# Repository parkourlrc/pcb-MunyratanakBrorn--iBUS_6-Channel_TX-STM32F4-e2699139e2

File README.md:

# iBUS_6-Channel_TX-STM32F4
iBUS Remote Controller using nRF24l01+

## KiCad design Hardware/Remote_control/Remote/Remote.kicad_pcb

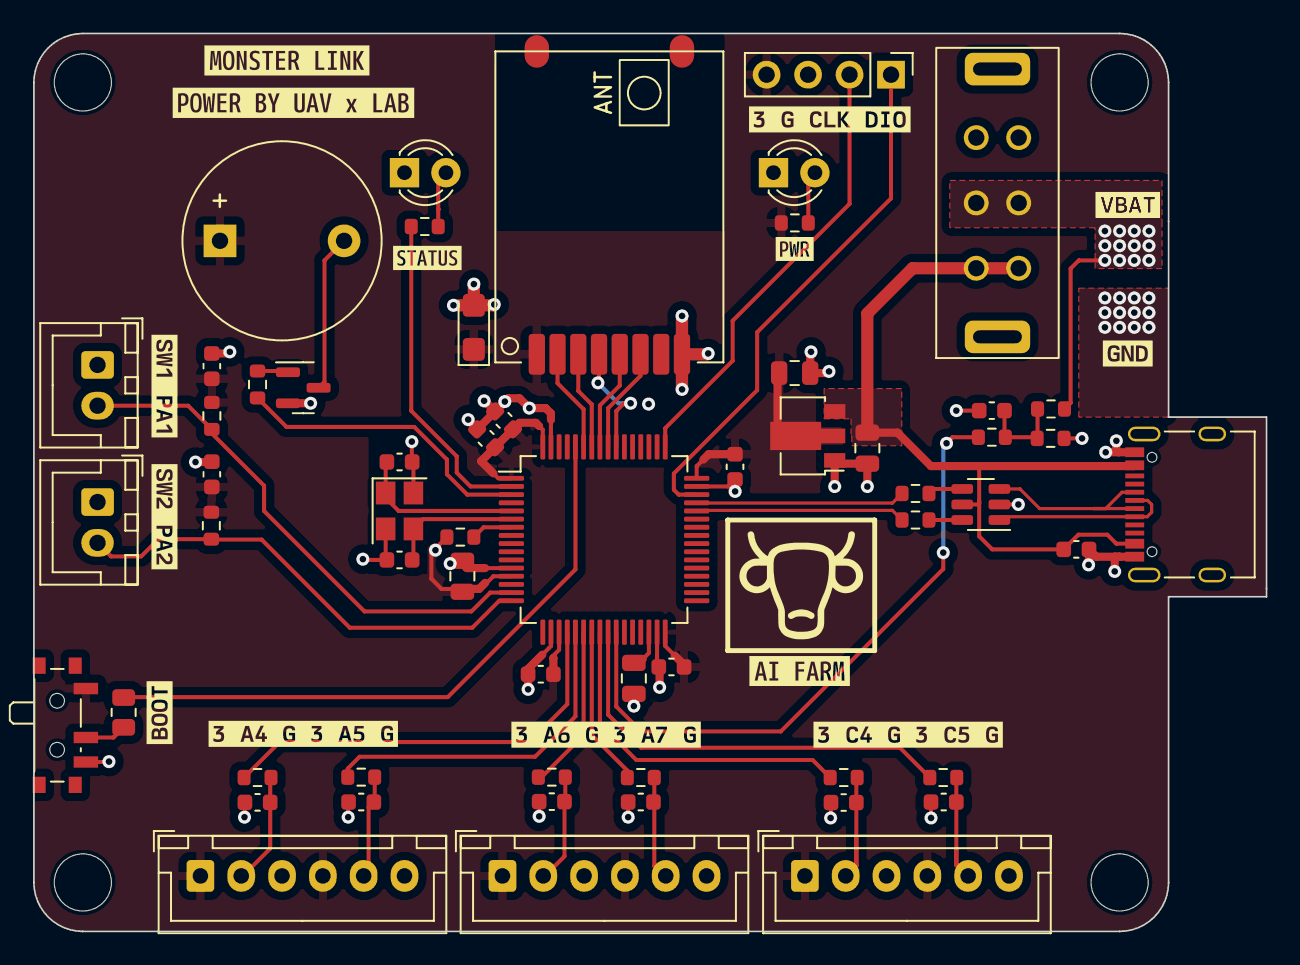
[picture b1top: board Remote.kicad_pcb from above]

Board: 2 copper layers, 75.5 x 55.0 mm, 77 parts (0 on the bottom side), 45 nets.

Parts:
BZ1: Buzzer; Buzzer_12x9.5RM7.6
C1, C6, C7, C8, C9, C10, C16, C17, C18, C19, C20, C21, C22, C24, C25: 100nf; C_0603_1608Metric
C3, C11: 4.7uF; C_0805_2012Metric
C5: 100nf; C_0805_2012Metric
C12: 2.2uF; C_0805_2012Metric
C13, C14: 22PF; C_0603_1608Metric
C15: 4.7UF; CP_EIA-3216-12_Kemet-S
D2, D3: LED; LED_D3.0mm
H1, H2, H3, H4: MountingHole; MountingHole_3.5mm
J1: USB_C_Receptacle_USB2.0; USB_C_Receptacle_Palconn_UTC16-G
J2: SL_LINK; PinHeader_1x04_P2.54mm_Vertical
J3, J5, J6: ADC; JST_XH_B6B-XH-A_1x06_P2.50mm_Vertical
J4, J8: SW; JST_XH_B2B-XH-A_1x02_P2.50mm_Vertical
Q1: 1P; SOT-23
R1, R4: 22; R_0603_1608Metric
R2, R5, R11, R12, R13, R14, R15, R16, R17: 1K; R_0603_1608Metric
R3: 4.7K; R_0603_1608Metric
R6, R9: 1k; R_0603_1608Metric
R7: 10k; R_0805_2012Metric
R8: 10k; R_0603_1608Metric
R10: 470R; R_0603_1608Metric
R18: 3K; R_0603_1608Metric
SW1: SW_SPDT; SW_SPDT_PCM12
U2: STM32F401RCTx; LQFP-64_10x10mm_P0.5mm
U3: AMS1117-3.3; SOT-89-3
U4: AS01-SPI
U5: USBLC6-2SC6; SOT-23-6
U6: Slide-Switch
Y1: 8Mhz; Crystal_SMD_3225-4Pin_3.2x2.5mm
kibuzzard-64B61BBF, kibuzzard-64B61BBF#2: G***; kibuzzard-64B61BBF
kibuzzard-64B61BC8: G***; kibuzzard-64B61BC8
kibuzzard-64B63D2D: G***; kibuzzard-64B63D2D
kibuzzard-64B63D22: G***; kibuzzard-64B63D22
kibuzzard-64B63D40: G***; kibuzzard-64B63D40
kibuzzard-64B634B2: G***; kibuzzard-64B634B2
kibuzzard-64B63325: G***; kibuzzard-64B63325
kibuzzard-64B63473: G***; kibuzzard-64B63473
kibuzzard-64B63542: G***; kibuzzard-64B63542
kibuzzard-64C36C76: G***; kibuzzard-64C36C76
kibuzzard-64C36CB1: G***; kibuzzard-64C36CB1
kibuzzard-64C36CD5: G***; kibuzzard-64C36CD5
kibuzzard-64C36D1E: G***; kibuzzard-64C36D1E
kibuzzard-64C36D15: G***; kibuzzard-64C36D15

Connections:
+3.3V: BZ1.1 (-), C5.2, C6.2, C7.2, C8.2, C9.2, C10.2, C11.1, C15.1, C24.1, C25.1, J2.4, J3.1, J3.4, J5.1, J5.4, J6.1, J6.4, R6.1, R8.1, R11.2, R12.2, SW1.1 (A), U2.1 (VBAT), U2.13 (VREF+), U2.19 (VDD), U2.32 (VDD), U2.48 (VDD), U2.64 (VDD), U3.2 (VO), U4.1 (VCC)
+5V: C3.1, C16.2, J1.A4 (VBUS), J1.A9 (VBUS), J1.B4 (VBUS), J1.B9 (VBUS), U3.3 (VI), U5.5 (VBUS), U6.1, U6.4
/ADC1: C17.2, J3.5, R5.2
/ADC2: C18.2, J3.2, R13.2
/ADC3: C19.2, J5.2, R14.2
/ADC4: C20.2, J5.5, R15.2
/ADC5: C21.2, J6.2, R16.2
/ADC6: C22.2, J6.5, R17.2
/ADC_PA4: R13.1, U2.20 (PA4)
/ADC_PA5: R5.1, U2.21 (PA5)
/ADC_PA6: R14.1, U2.22 (PA6)
/ADC_PA7: R15.1, U2.23 (PA7)
/ADC_PB0: R2.1, U2.26 (PB0)
/ADC_PC4: R16.1, U2.24 (PC4)
/ADC_PC5: R17.1, U2.25 (PC5)
/BOOT0: R7.1, U2.60 (BOOT0)
/CE_PB7: U2.59 (PB7), U4.2 (CE)
/CLK: J2.2, U2.49 (PA14)
/CSN_PB6: U2.58 (PB6), U4.3 (CSN)
/DIO: J2.1, U2.46 (PA13)
/LED: R9.1, U2.2 (PC13)
/MISO_PB4: U2.56 (PB4), U4.6 (MISO)
/MOSI_PB5: U2.57 (PB5), U4.5 (MOSI)
/NRST: R8.2, U2.7 (NRST)
/OSC_IN: C13.1, U2.5 (PH0), Y1.1
/OSC_OUT: C14.1, U2.6 (PH1), Y1.3
/PA1_SW1: J8.2, R12.1, U2.15 (PA1)
/PA2_SW2: J4.2, R11.1, U2.16 (PA2)
/PC14_BUZZER: R10.1, U2.3 (PC14)
/SCK_PB3: U2.55 (PB3), U4.4 (CLK)
/USB_IN+: J1.A6 (D+), J1.B6 (D+), U5.3 (I/O2)
/USB_IN-: J1.A7 (D-), J1.B7 (D-), U5.1 (I/O1)
/USB_OUT+: R1.2, U2.45 (PA12)
/USB_OUT-: R4.1, U2.44 (PA11)
/VBAT: R3.2, U6.2, U6.5
/VBAT_MEASURE: C1.2, R2.2, R3.1, R18.2
GND: C1.1, C3.2, C5.1, C6.1, C7.1, C8.1, C9.1, C10.1, C11.2, C12.2, C13.2, C14.2, C15.2, C16.1, C17.1, C18.1, C19.1, C20.1, C21.1, C22.1, C24.2, C25.2, D2.1 (K), D3.1 (K), J1.A1 (GND), J1.A12 (GND), J1.B1 (GND), J1.B12 (GND), J1.S1 (SHIELD), J2.3, J3.3, J3.6, J4.1, J5.3, J5.6, J6.3, J6.6, J8.1, Q1.2 (E), R18.1, SW1.3 (C), U2.12 (VSSA), U2.18 (VSS), U2.31 (VSS), U2.47 (VSS), U2.63 (VSS), U3.1 (GND), U4.8 (GND), U5.2 (GND), Y1.2, Y1.4
unnamed: BZ1.2 (+), Q1.3 (C)
unnamed: D2.2 (A), R6.2
unnamed: D3.2 (A), R9.2
unnamed: Q1.1 (B), R10.2
unnamed: R1.1, U5.4 (I/O2)
unnamed: R4.2, U5.6 (I/O1)
unnamed: R7.2, SW1.2 (B)
unnamed: C12.1, U2.30 (VCAP1)

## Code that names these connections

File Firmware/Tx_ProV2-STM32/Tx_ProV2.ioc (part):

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Mcu.Name=STM32F401R(B-C)Tx
Mcu.Package=LQFP64
Mcu.UserName=STM32F401RCTx
PA1.GPIOParameters=GPIO_Label
PA1.GPIO_Label=swa
PA1.Signal=GPIO_Input
PA13.Mode=Serial_Wire
PA13.Signal=SYS_JTMS-SWDIO
PA14.Mode=Serial_Wire
PA14.Signal=SYS_JTCK-SWCLK
PA2.GPIOParameters=GPIO_Label
PA2.GPIO_Label=swb
PA2.Signal=GPIO_Input
PA4.Signal=ADCx_IN4
PA5.Signal=ADCx_IN5
PB3.Mode=Full_Duplex_Master
PB3.Signal=SPI1_SCK
PB4.Mode=Full_Duplex_Master
PB4.Signal=SPI1_MISO
PB5.Mode=Full_Duplex_Master
PB5.Signal=SPI1_MOSI
PB6.GPIOParameters=GPIO_Label
PB6.GPIO_Label=SPI1_CNS
PB6.Signal=GPIO_Output
PB7.GPIOParameters=GPIO_Label
PB7.GPIO_Label=SPI1_CE
PB7.Signal=GPIO_Output
PC13-ANTI_TAMP.GPIOParameters=GPIO_Label
PC13-ANTI_TAMP.GPIO_Label=LED
PC13-ANTI_TAMP.Signal=GPIO_Output
PC14-OSC32_IN.GPIOParameters=GPIO_Label
PC14-OSC32_IN.GPIO_Label=Buzz
PC14-OSC32_IN.Signal=GPIO_Output
PC15-OSC32_OUT.Signal=GPIO_Input
PC4.Signal=ADCx_IN14
PC5.Signal=ADCx_IN15
PH0\ -\ OSC_IN.Mode=HSE-External-Oscillator
PH0\ -\ OSC_IN.Signal=RCC_OSC_IN
PH1\ -\ OSC_OUT.Mode=HSE-External-Oscillator
PH1\ -\ OSC_OUT.Signal=RCC_OSC_OUT
RCC.HSE_VALUE=8000000
RCC.SYSCLKFreq_VALUE=84000000
RCC.SYSCLKSource=RCC_SYSCLKSOURCE_PLLCLK
board=custom
